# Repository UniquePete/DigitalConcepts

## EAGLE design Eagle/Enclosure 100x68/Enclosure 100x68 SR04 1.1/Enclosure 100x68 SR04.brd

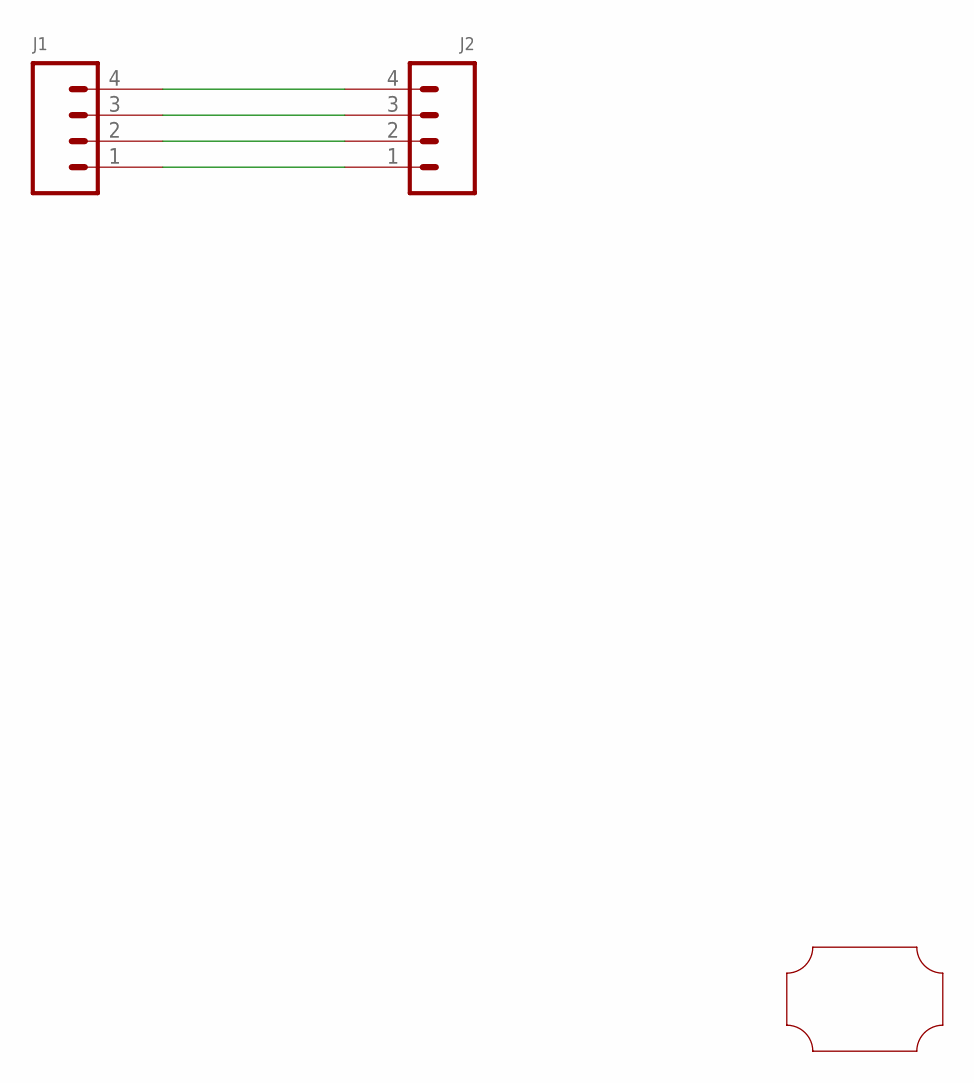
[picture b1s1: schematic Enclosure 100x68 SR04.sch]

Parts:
J1: HEADER-1X4-GENERIC; CONN_04-GENERIC
J2: JST-XH2.54-4-HORIZONTAL; JST-XH2.4-4-HORIZONTAL
U$1: PROTO-34X22-SR04

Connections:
unnamed: J1.4, J2.4
unnamed: J1.3, J2.3
unnamed: J1.2, J2.2
unnamed: J1.1, J2.1

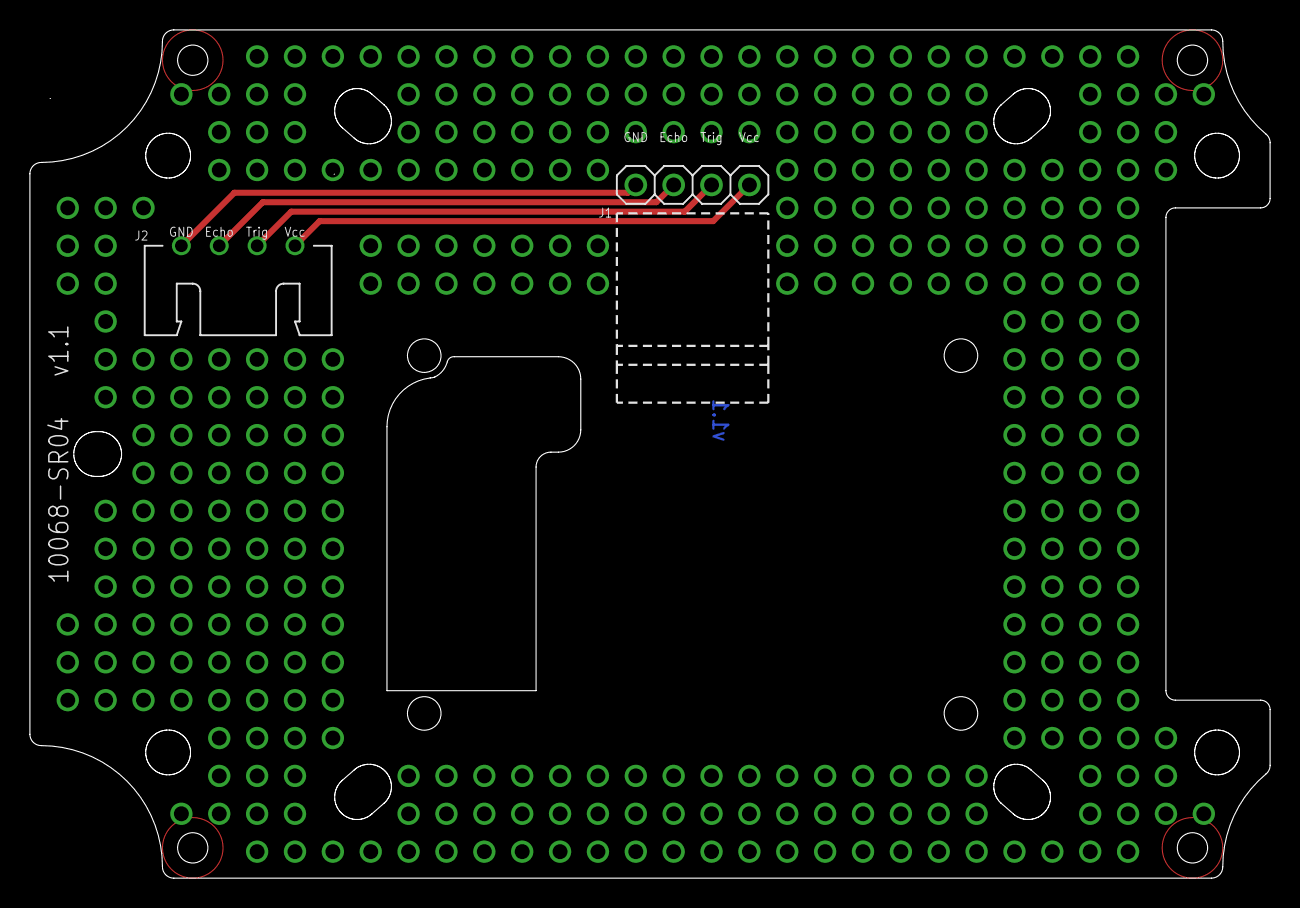
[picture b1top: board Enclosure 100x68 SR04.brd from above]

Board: 2 copper layers, 83.2 x 56.9 mm, 3 parts (0 on the bottom side), 4 nets.

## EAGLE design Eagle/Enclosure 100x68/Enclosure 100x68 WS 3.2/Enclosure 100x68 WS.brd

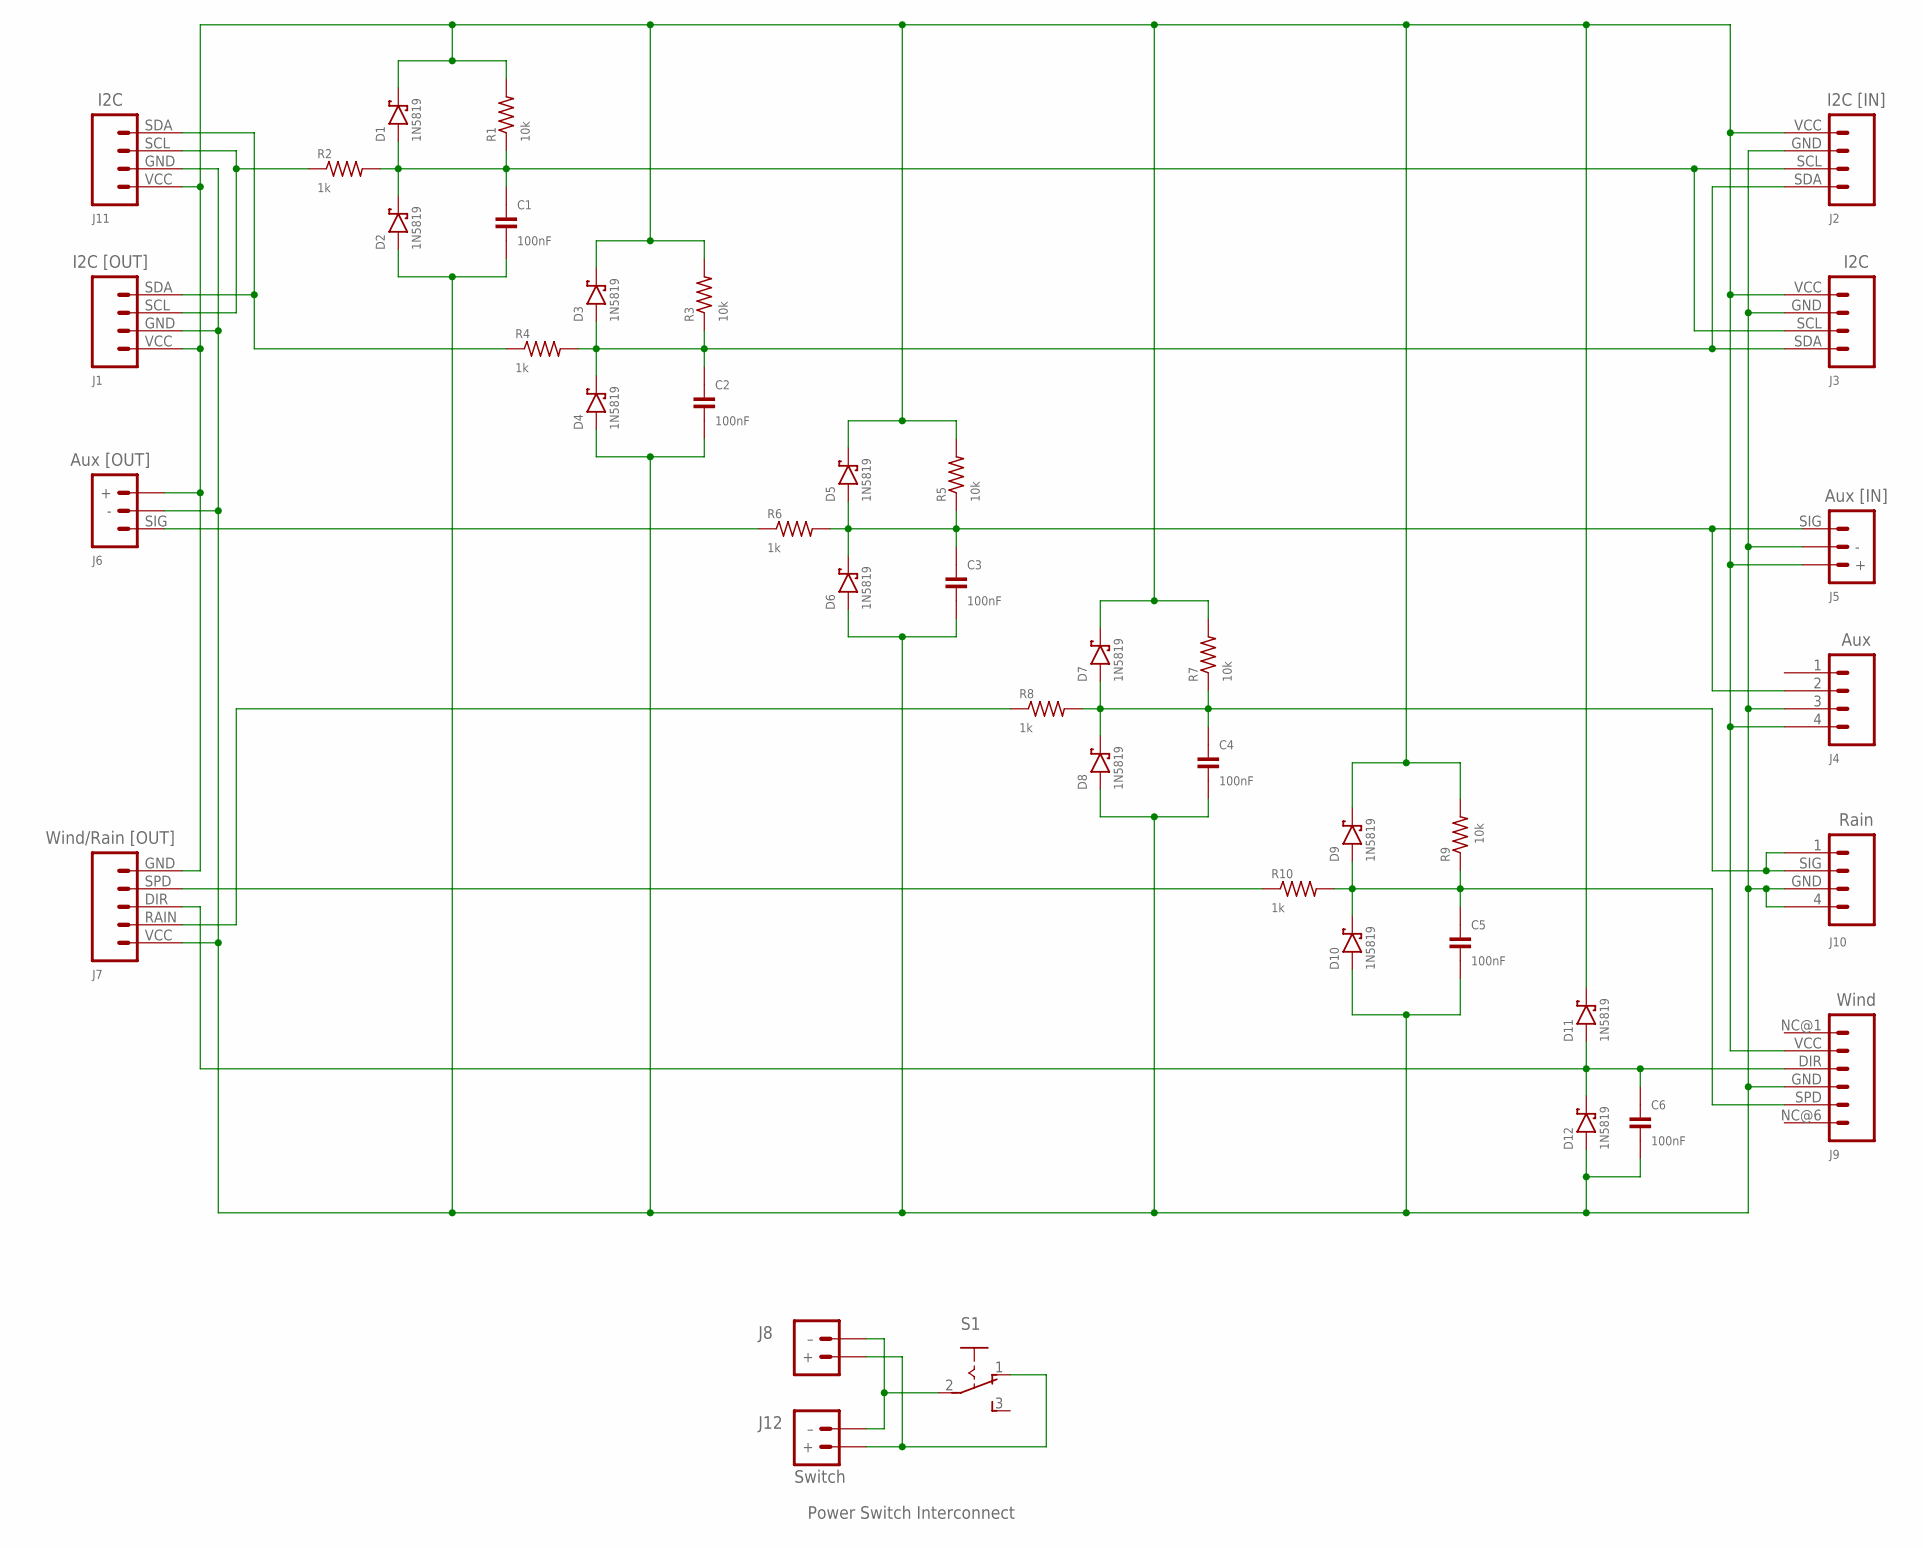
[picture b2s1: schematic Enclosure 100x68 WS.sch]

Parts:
C1, C2, C3, C4, C5, C6: 100nF; C0805
D1, D2, D3, D4, D5, D6, D7, D8, D9, D10, D11, D12: 1N5819; SOD-123
J1: I2C [OUT]; JST-PH2.0-4-DUAL-I2C
J2: I2C [IN]; JST-PH2.0-4-VERTICAL-I2C
J3: I2C; RJ11-4-VERTICAL-I2C
J4: Aux; RJ11-4-VERTICAL
J5: Aux [IN]; JST-PH2.0-3-VERTICAL-SIG
J6: Aux [OUT]; JST-PH2.0-3-DUAL-SIG
J7: Wind/Rain [OUT]; JST-PH2.0-5-DUAL-WEATHER
J8: Switch; JST-PH2.0-2-VERTICAL=POWER
J9: Wind; RJ11-6-VERTICAL-WIND
J10: Rain; RJ11-4-VERTICAL-RAIN
J11: I2C; CONN_04-I2C
J12: Switch; JST-PH2.0-2-HORIZONTAL-POWER
R1, R3, R5, R7, R9: 10k; R0805
R2, R4, R6, R8, R10: 1k; R0805
S1: SWITCH-SLIDE-SPDT; SWITCH-SPDT-PTH

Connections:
GND: C1.2, C2.2, C3.2, C4.2, C5.2, C6.2, D2.A, D4.A, D6.A, D8.A, D10.A, D12.A, J1.GND (2), J2.GND (2), J3.GND (2), J4.3, J5.-, J6.-, J7.VCC (1), J9.GND (4), J10.4, J10.GND (3), J11.GND (2)
unnamed: J7.RAIN (2), R8.1
unnamed: J1.SCL (3), J11.SCL (3), R2.1
unnamed: J1.SDA (4), J11.SDA (4), R4.1
unnamed: C6.1, D11.A, D12.C, J7.DIR (3), J9.DIR (3)
unnamed: J7.SPD (4), R10.1
unnamed: C4.1, D7.A, D8.C, J10.1, J10.SIG (2), R7.1, R8.2
unnamed: C2.1, D3.A, D4.C, J2.SDA (4), J3.SDA (4), R3.1, R4.2
unnamed: J6.SIG, R6.1
unnamed: C1.1, D1.A, D2.C, J2.SCL (3), J3.SCL (3), R1.1, R2.2
unnamed: J8.- (–), J12.- (–), S1.2
unnamed: C3.1, D5.A, D6.C, J4.2, J5.SIG, R5.1, R6.2
unnamed: J8.+, J12.+, S1.1 (O)
unnamed: C5.1, D9.A, D10.C, J9.SPD (5), R9.1, R10.2
VCC: D1.C, D3.C, D5.C, D7.C, D9.C, D11.C, J1.VCC (1), J2.VCC (1), J3.VCC (1), J4.4, J5.+, J6.+, J7.GND (5), J9.VCC (2), J11.VCC (1), R1.2, R3.2, R5.2, R7.2, R9.2

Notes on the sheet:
Power Switch Interconnect

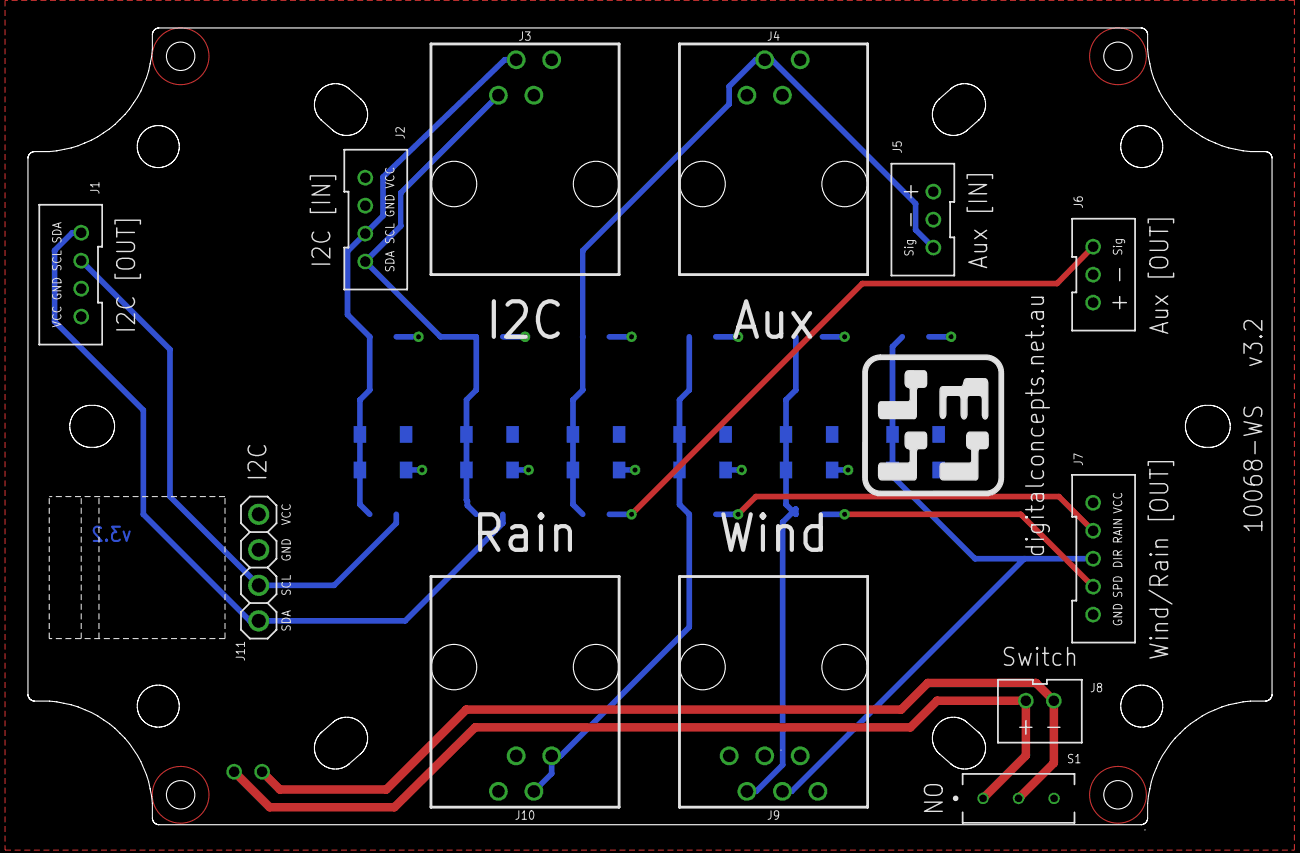
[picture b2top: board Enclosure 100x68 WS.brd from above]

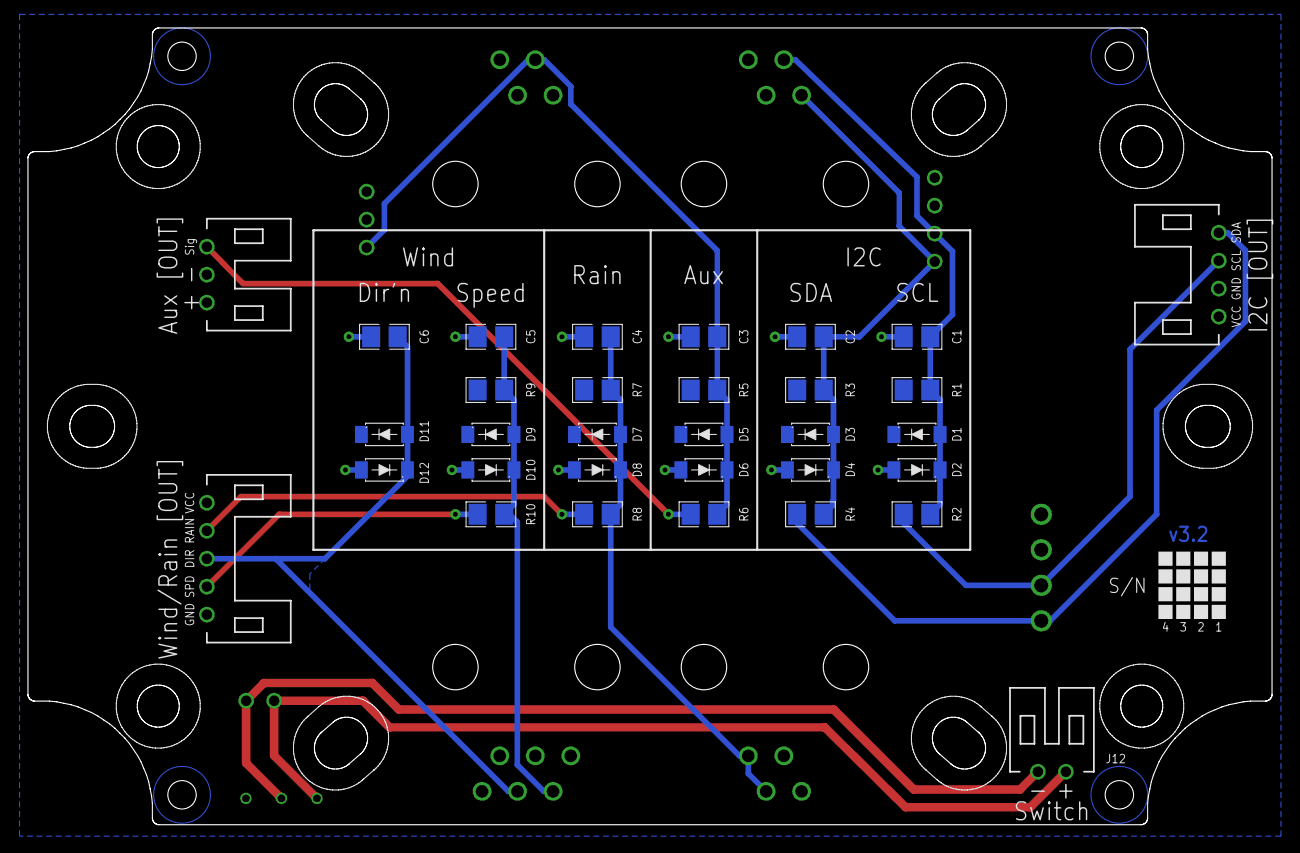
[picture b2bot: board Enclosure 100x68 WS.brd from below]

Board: 2 copper layers, 89.0 x 57.0 mm, 41 parts (32 on the bottom side), 15 nets.

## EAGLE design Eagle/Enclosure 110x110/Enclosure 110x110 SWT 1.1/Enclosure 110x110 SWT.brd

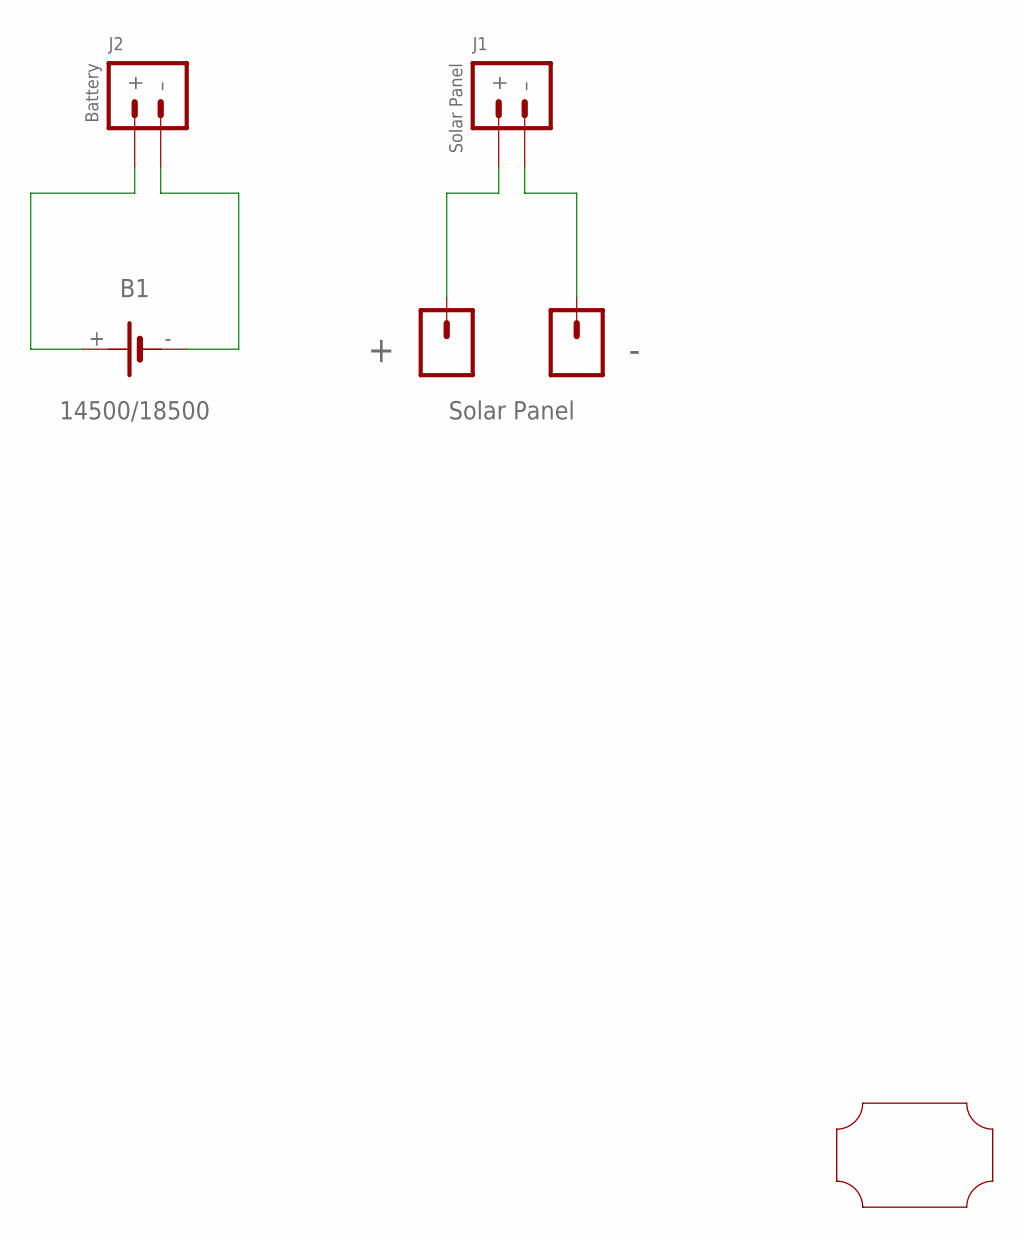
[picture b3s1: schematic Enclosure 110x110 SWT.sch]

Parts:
+: PAD-SMD-GENERIC-SQUARE; PAD-SMD-GENERIC
-: PAD-SMD-GENERIC-SQUARE; PAD-SMD-GENERIC
B1: 14500/18500; BATTERY-14500/18500
J1: Solar Panel; JST-PH2.0-2-HORIZONTAL-POWER
J2: Battery; JST-PH2.0-2-HORIZONTAL-POWER
U$1: PCB-OUTLINE-110X110; PROTO-110X110-OUTLINE

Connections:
unnamed: B1.+, J2.+
unnamed: B1.-, J2.- (–)
unnamed: +.P$1, J1.+
unnamed: -.P$1, J1.- (–)

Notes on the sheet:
Solar Panel

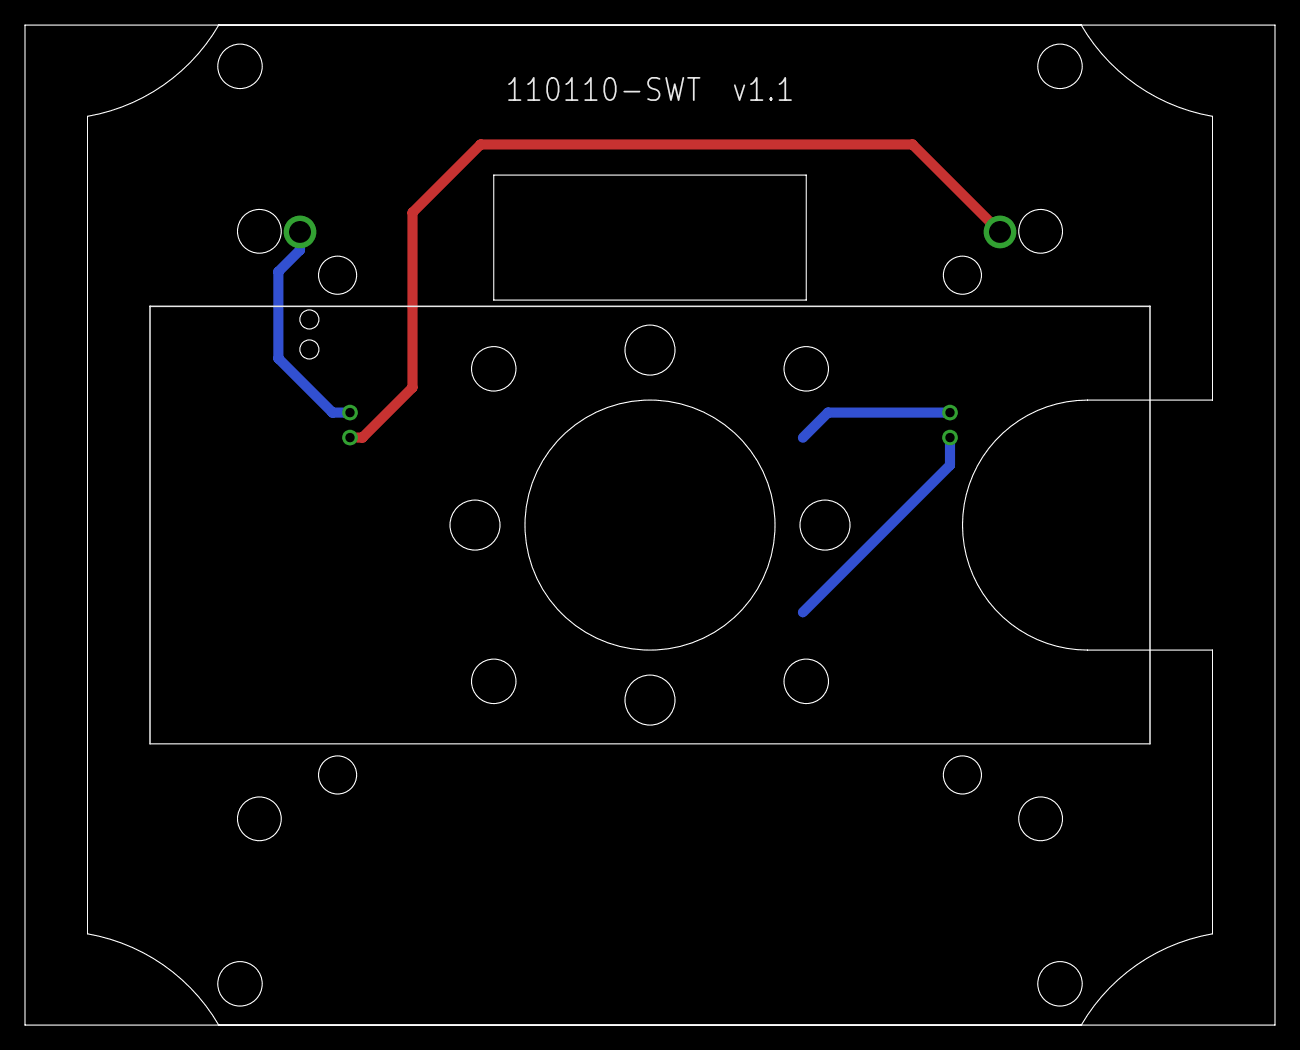
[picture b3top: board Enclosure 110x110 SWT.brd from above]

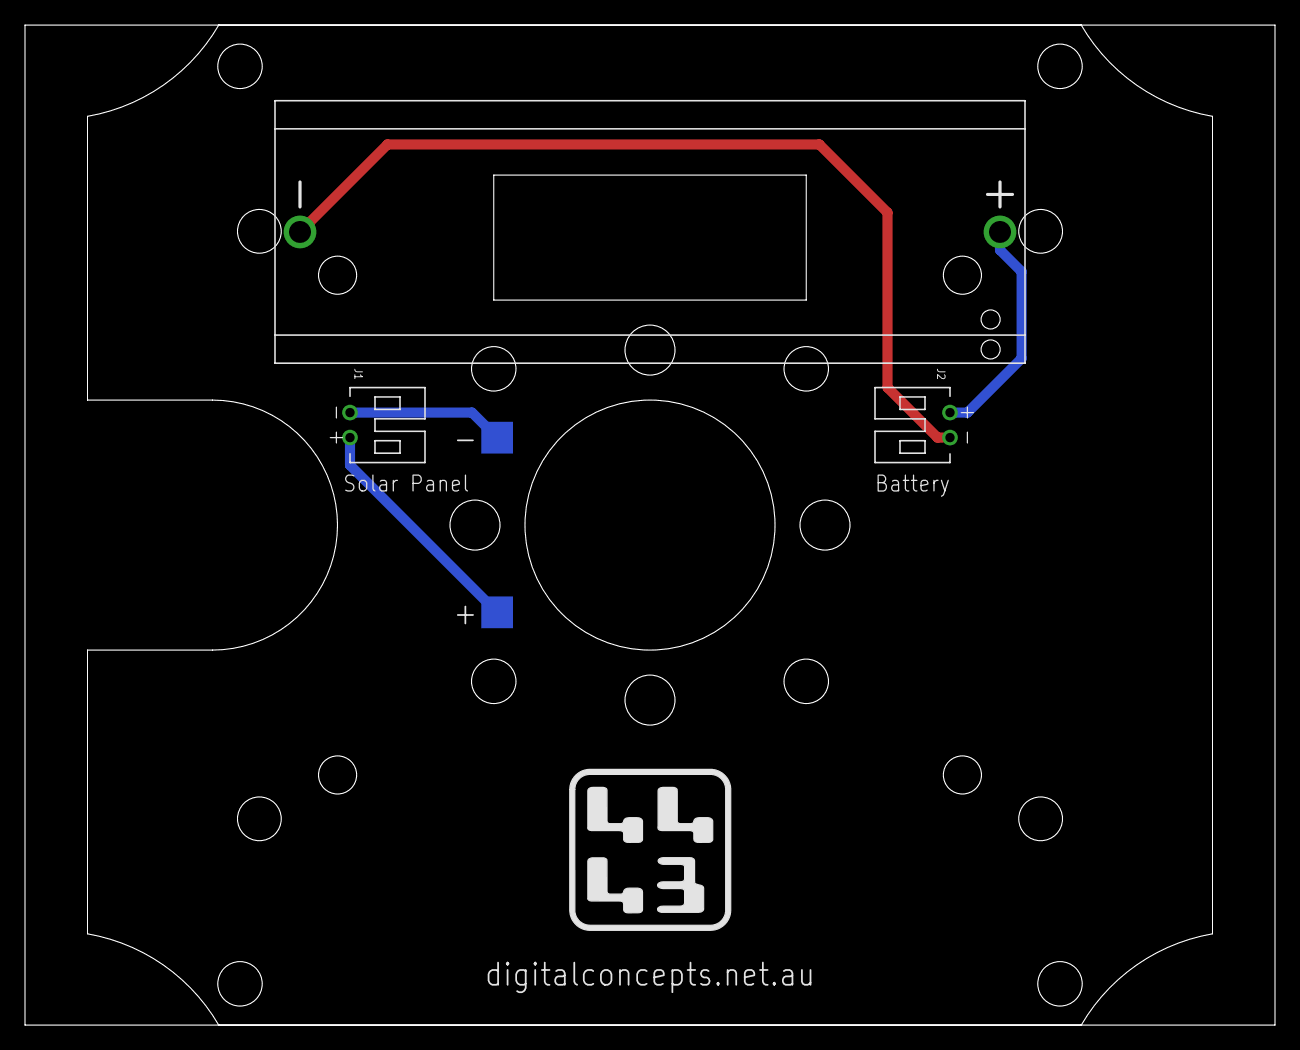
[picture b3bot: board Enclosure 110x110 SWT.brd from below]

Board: 2 copper layers, 100.0 x 80.0 mm, 6 parts (5 on the bottom side), 4 nets.

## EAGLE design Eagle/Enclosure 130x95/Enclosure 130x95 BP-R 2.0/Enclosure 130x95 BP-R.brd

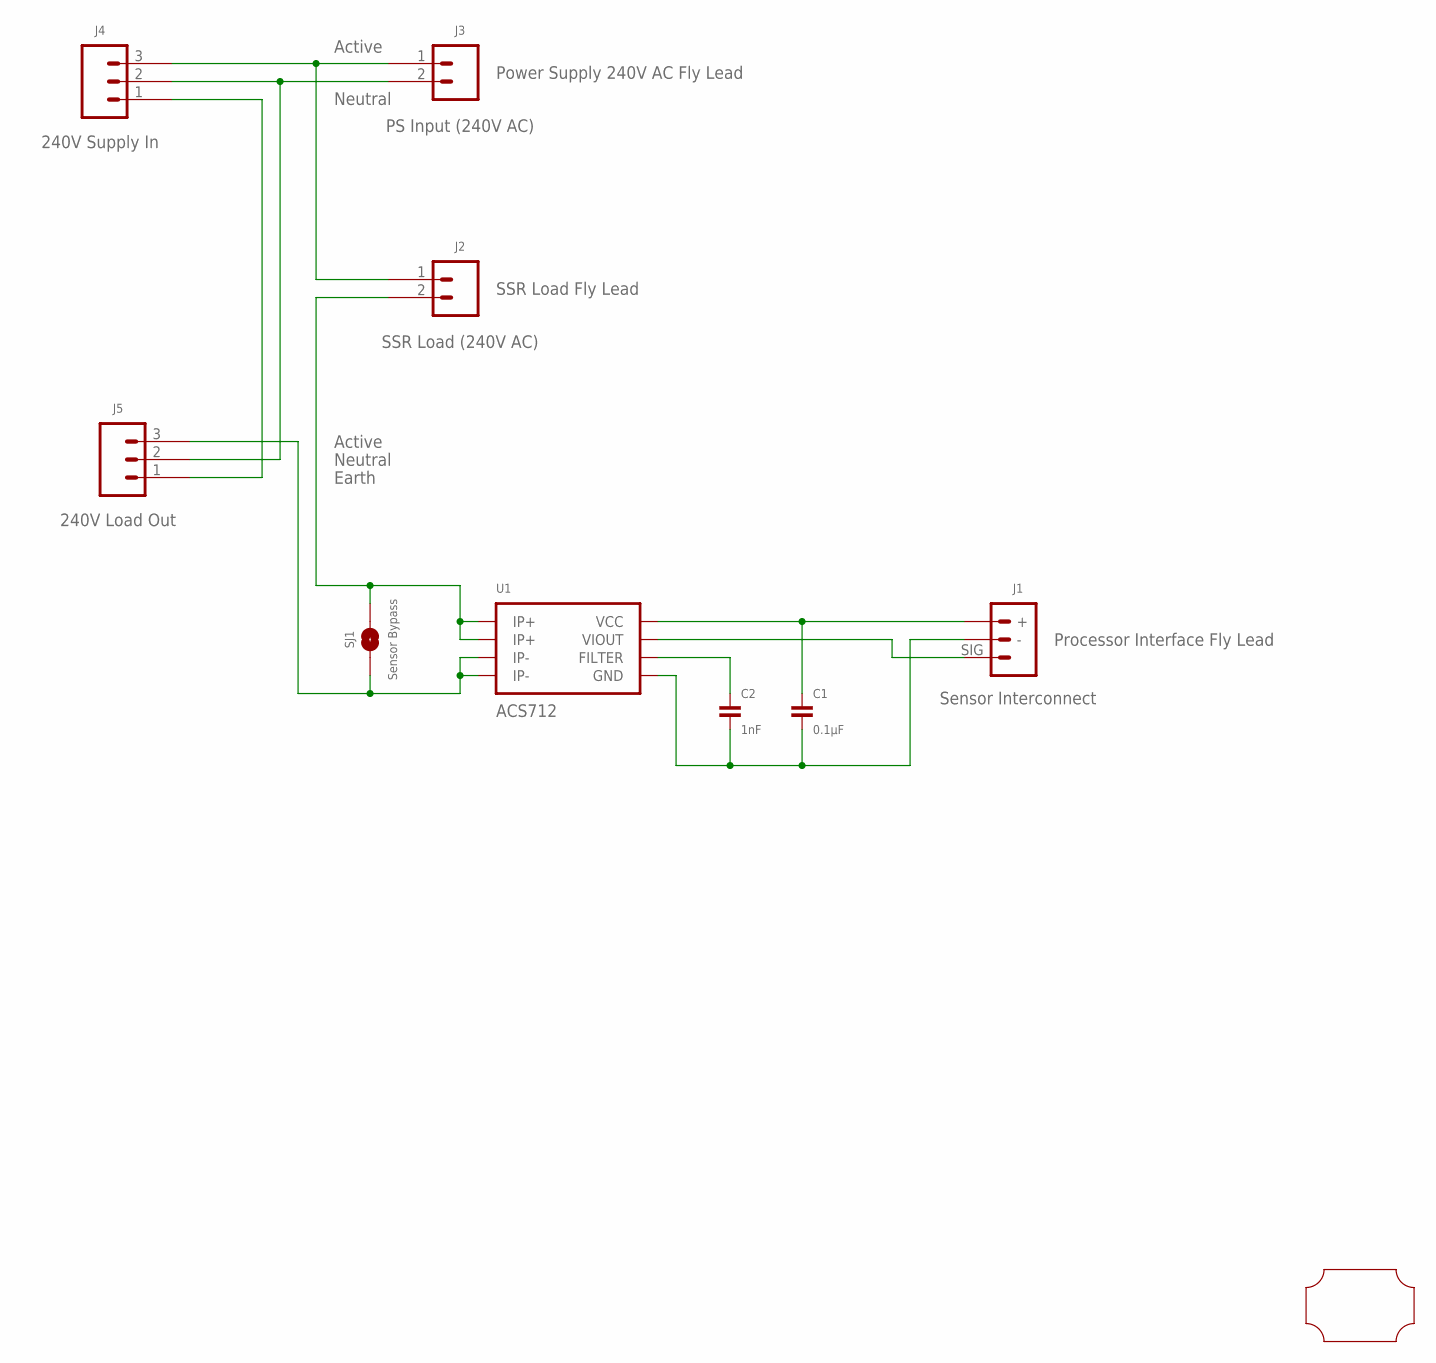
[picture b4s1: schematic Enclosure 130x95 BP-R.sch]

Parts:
C1: 0.1µF; C0805
C2: 1nF; C0805
J1: Sensor Interconnect; JST-PH2.0-3-HORIZONTAL-SIG
J2: SSR Load (240V AC); TERMINAL-SCREW-2P
J3: PS Input (240V AC); JST-XH2.4-2-HORIZONTAL
J4: 240V Supply In; TERMINAL-SCREW-3P
J5: 240V Load Out; TERMINAL-SCREW-3P
SJ1: Sensor Bypass; SJ
U1: ACS712; SOIC-8
U$1: PCB-OUTLINE-130X95-MAX-RC-H2; PROTO-130X95-OUTLINE-MAX-RC-H2

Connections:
ACTIVE_IN: J2.1, J3.1, J4.3
ACTIVE_OUT: J2.2, SJ1.2, U1.P$1 (IP+), U1.P$2 (IP+)
EARTH: J4.1, J5.1
unnamed: J5.3, SJ1.1, U1.P$3 (IP-), U1.P$4 (IP-)
unnamed: C1.2, C2.2, J1.-, U1.P$5 (GND)
unnamed: J1.SIG, U1.P$7 (VIOUT)
unnamed: C1.1, J1.+, U1.P$8 (VCC)
unnamed: C2.1, U1.P$6 (FILTER)
NEUTRAL: J3.2, J4.2, J5.2

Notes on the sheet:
Power Supply 240V AC Fly Lead
Active
Neutral
SSR Load Fly Lead
Earth
Processor Interface Fly Lead

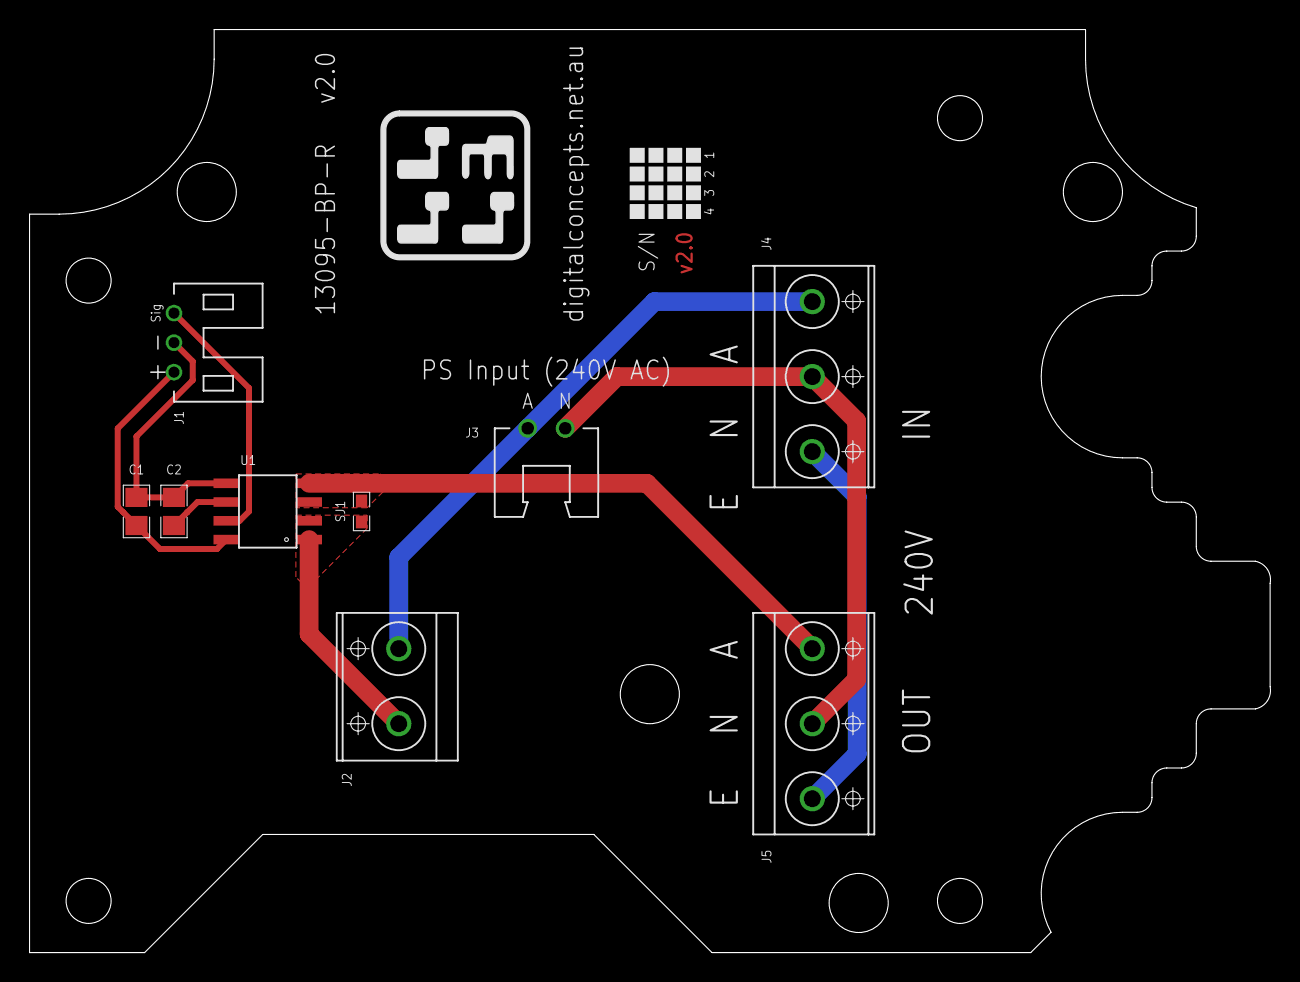
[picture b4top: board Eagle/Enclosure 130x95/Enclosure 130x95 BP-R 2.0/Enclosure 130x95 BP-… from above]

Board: 2 copper layers, 84.0 x 62.5 mm, 10 parts (0 on the bottom side), 9 nets.

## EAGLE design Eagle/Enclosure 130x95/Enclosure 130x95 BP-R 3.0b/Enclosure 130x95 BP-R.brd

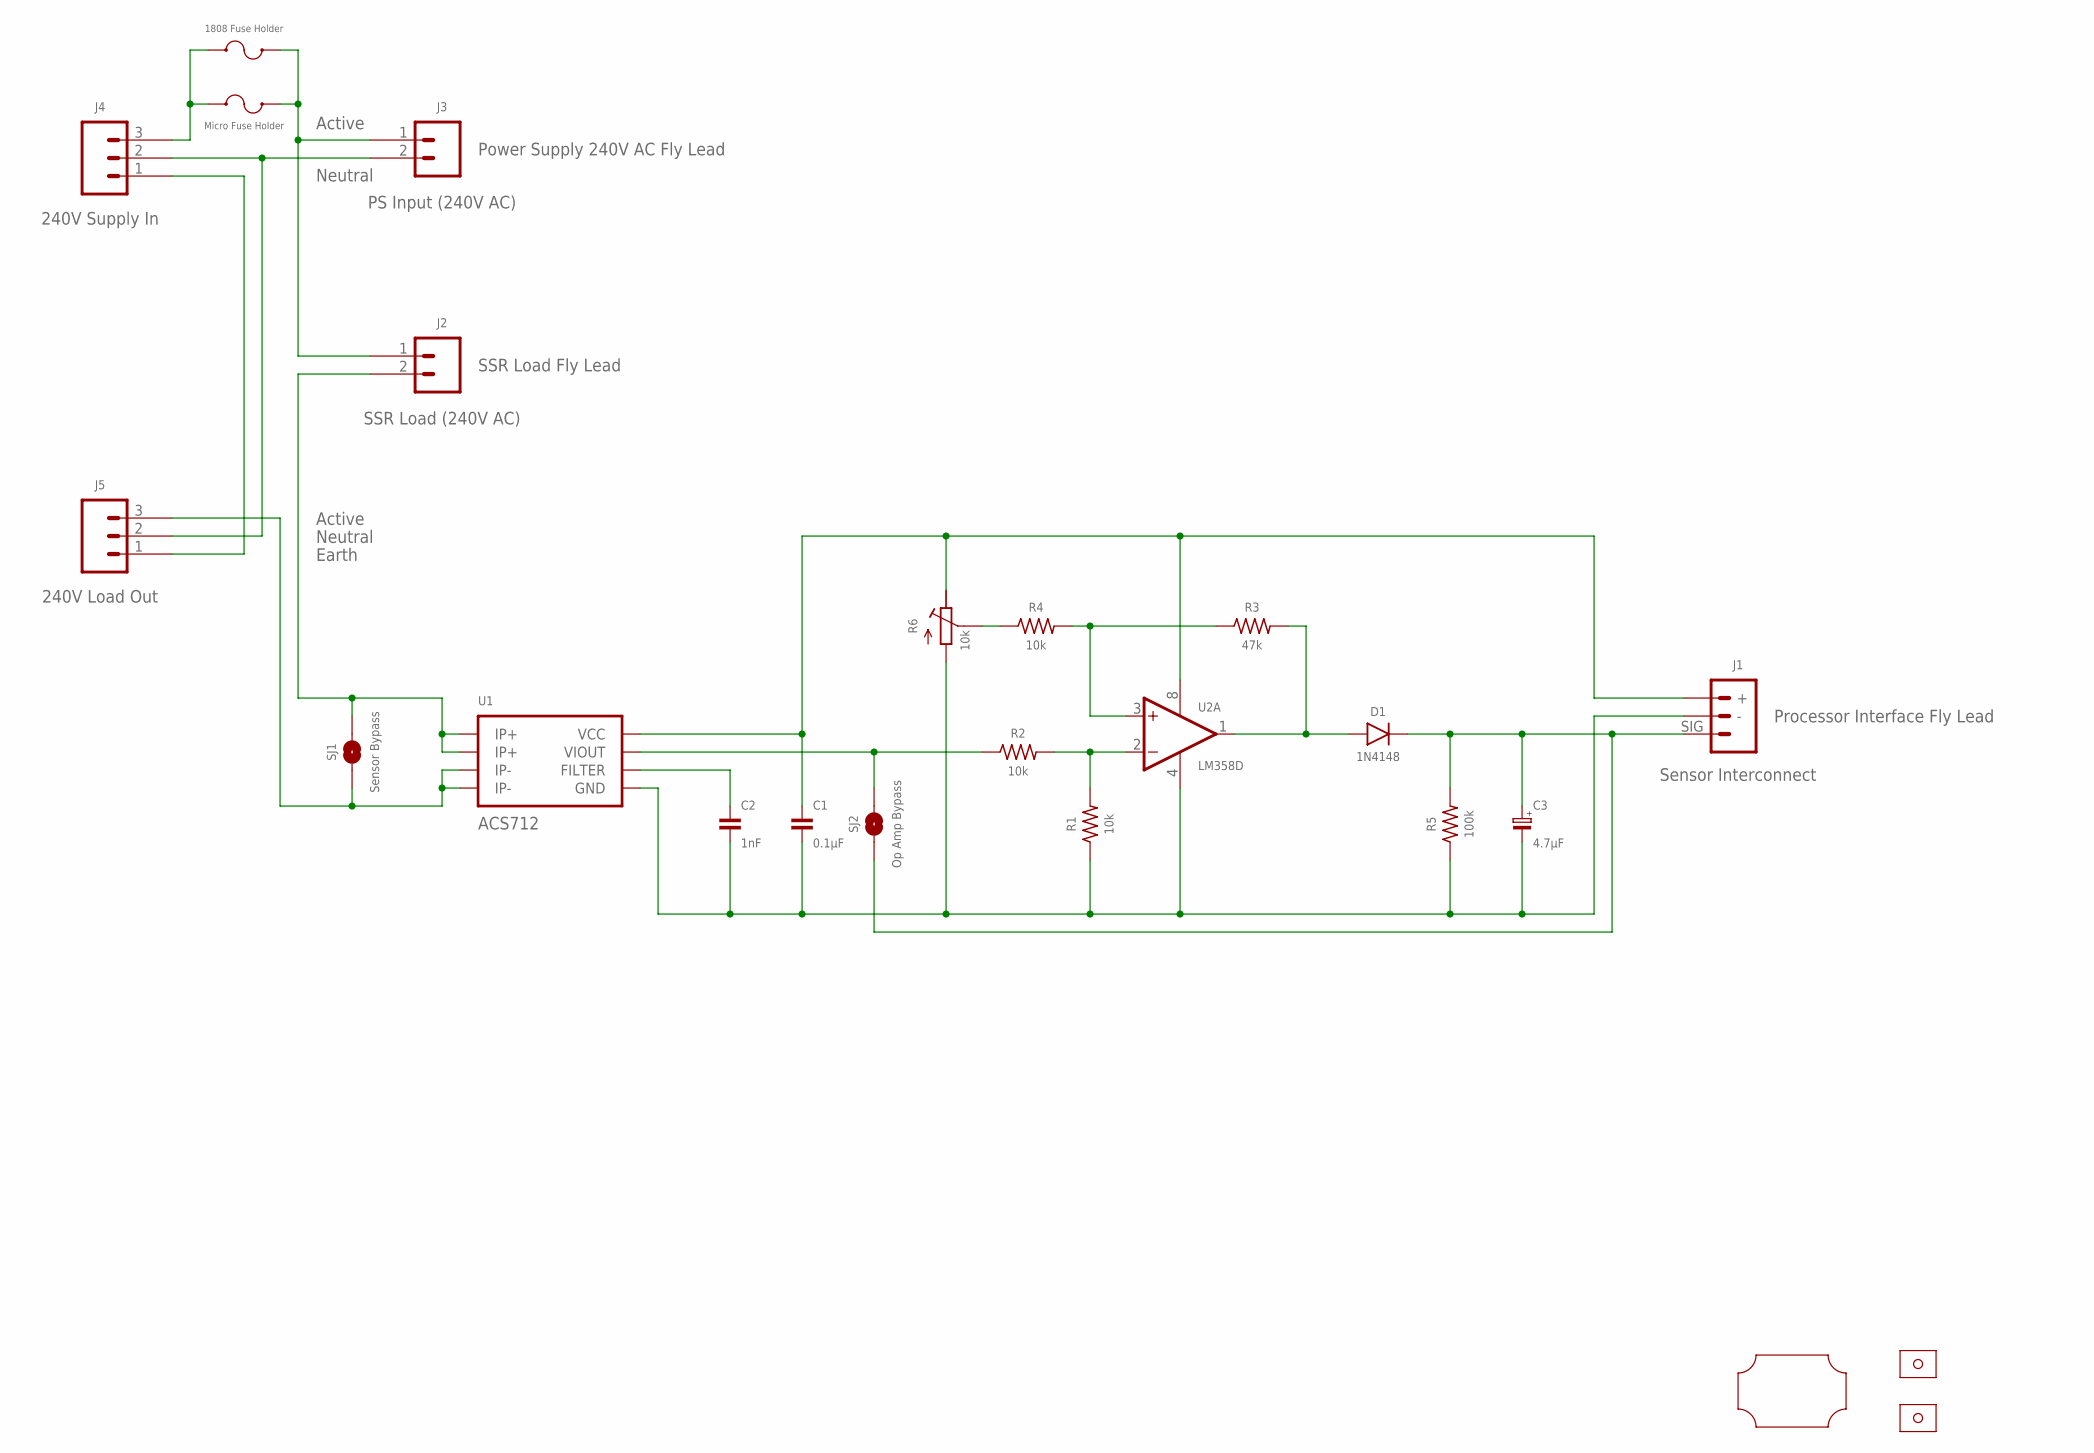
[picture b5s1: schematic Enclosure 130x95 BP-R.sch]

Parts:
C1: 0.1µF; C0805
C2: 1nF; C0805
C3: 4.7µF; C1206-POLARISED
D1: 1N4148; SOD-323
F2: 1808 Fuse Holder; FUSE-HOLDER-1808
J1: Sensor Interconnect; JST-PH2.0-3-HORIZONTAL-SIG
J2: SSR Load (240V AC); TERMINAL-SCREW-2P
J3: PS Input (240V AC); JST-XH2.4-2-HORIZONTAL
J4: 240V Supply In; TERMINAL-SCREW-3P
J5: 240V Load Out; TERMINAL-SCREW-3P
R1, R2, R4: 10k; R0805
R3: 47k; R0805
R5: 100k; R0805
R6: 10k; RTRIM3386P
SJ1: Sensor Bypass; SJ
SJ2: Op Amp Bypass; SJ
U1: ACS712; SOP-8
U2: LM358D; SOP-8
U$1: PCB-OUTLINE-130X95-MAX-RC-H3; PROTO-130X95-OUTLINE-MAX-RC-H3
U$2: Micro Fuse Holder; FUSE-HOLDER-MICRO
U$4, U$5: STRAIN-RELIEF-SADDLE

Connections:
ACTIVE_IN: F2.P$2 (2), J2.1, J3.1, U$2.P$3 (2), U$2.P$4 (2)
ACTIVE_OUT: J2.2, SJ1.2, U1.1 (IP+), U1.2 (IP+)
EARTH: J4.1, J5.1
unnamed: C1.1, J1.+, R6.1 (E), U1.8 (VCC), U2.8 (V+)
unnamed: C3.1 (+), D1.C (1), J1.SIG, R5.2, SJ2.1
unnamed: D1.A (2), R3.2, U2.1 (OUT)
unnamed: R3.1, R4.2, U2.3 (+IN)
unnamed: R4.1, R6.2 (S)
unnamed: F2.P$1 (1), J4.3, U$2.P$1 (1), U$2.P$2 (1)
unnamed: R1.2, R2.2, U2.2 (-IN)
unnamed: J5.3, SJ1.1, U1.3 (IP-), U1.4 (IP-)
unnamed: C1.2, C2.2, C3.2 (-), J1.-, R1.1, R5.1, R6.3 (A), U1.5 (GND), U2.4 (V-)
unnamed: R2.1, SJ2.2, U1.7 (VIOUT)
unnamed: C2.1, U1.6 (FILTER)
NEUTRAL: J3.2, J4.2, J5.2

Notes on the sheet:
Power Supply 240V AC Fly Lead
Active
Neutral
SSR Load Fly Lead
Earth
Processor Interface Fly Lead

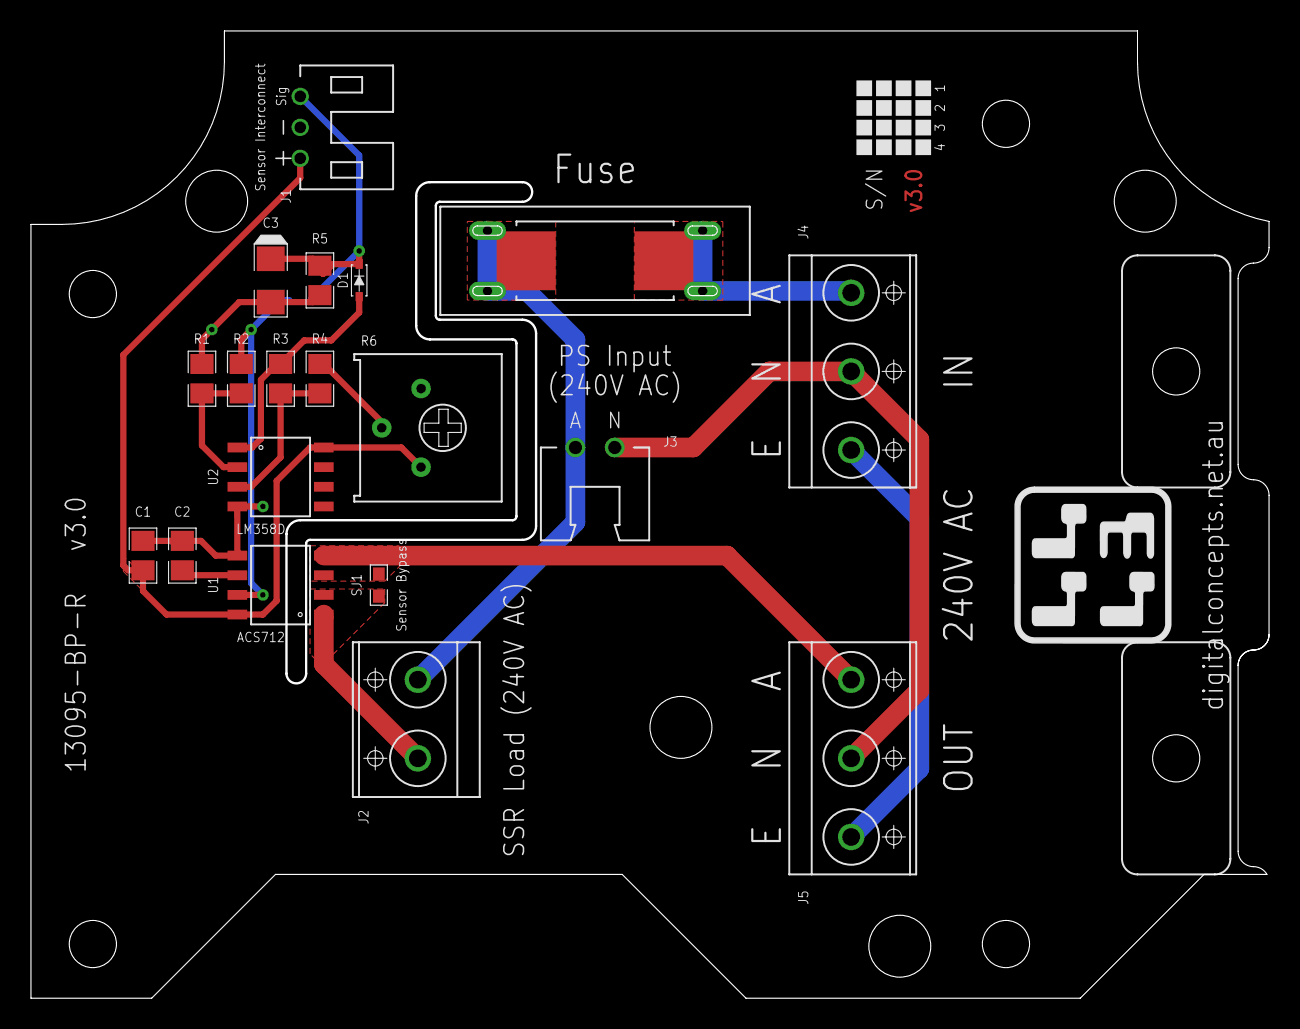
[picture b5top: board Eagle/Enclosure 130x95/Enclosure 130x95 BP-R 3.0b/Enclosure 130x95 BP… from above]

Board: 2 copper layers, 80.0 x 62.5 mm, 24 parts (1 on the bottom side), 15 nets.
